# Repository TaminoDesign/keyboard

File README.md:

# keyboard

 <br><br>
 <br><br>
 <br><br>

# Planning
30min (tracked with Lapse)
I have gone for a semi-custom 60% layout, which I think will work well for my needs. It is in a Mac-style layout (e.g., Command key and Option). You can find the sketch of the layout in the repo.

# Schematic
2 hours
Finished with the schematic layout, I had some trouble figuring out how to best arrange them and needed to do some research to find out if the exact placement was important at this point. Turns out the final sizes are only relevant in the next set, so could have saved myself some time. Well, anyway, looking good, moving on to the actual PCB

# PCB
(4:40min tracked with Lapse)
The PCB is finally done. I can't believe it took this long. I had so many issues; the first was realising that the switch cutouts need to be placed in the correct order, as in the schematic. Of course, I only realised this after placing all of them. The next thing to go wrong was realising that I had added too many rows to the schematic, so that had to change. And finally, it turns out I assigned the rows and columns in the wrong order, so I couldn't draw the traces on the board, meaning back to the schematic. To be honest, there still is the issue of switches over my Raspberry Pi; I'm not sure if it will work, but I think/hope that if it doesn't, I can just ignore those and cover them up (they are extra switches), so let's see. But the good news is that it's finished.

# PCB part 2
(2 hours tracked with lapse)
When you think something is finished but it isn't. In my original design, I had switches over top of the Pi; to be honest, I'm not sure if it would have been a problem, but I don't want to risk it. So I had to go and make changes to the schematic, and because I had already added all the tracks to the PCB and then moved switches about, that had to be redone. I mean, I'm glad I decided to do it; getting the PCB and finding that it doesn't work because of strange switch placement would have been so bad.

# Key switch research
(4 hours)
Yep, this was a rabbit hole if there ever was one. I knew a very little bit about the actual switches, just that there are three overall categories. So I really did spend 4 hours researching and comparing. Now I think I always knew I wanted linear switches; I have been typing on laptops my whole life, so I'm just so used to it. What really threw me was the sound: clicky, deep, silent, tappy, loud, medium or quiet. I pretty quickly found out I don't like the clicky to annoying and loud, then found some medium ones that were nice and deep and thought I had found the best ones. But when I thought about them being louder than my laptop, it just seemed too much (I need quiet to concentrate). So, abandoning everything, I started looking into silent switches, found out that silent doesn't really mean silent, just quieter and that even that varied a lot. After many sound tests and reading, I found the TTC Frozen V2 and the Outemu Peach V2. Those seem like the best ones for me; the TTCs are a little more expensive, but they are a lot nicer. I'm really not sure what the budget is, so if constrained, I will go for the Outemu; if not, then the TTC. Both are extremely quiet but still have a deeper sound signature and are not clacky. Well, that concluded my search, just have to find the rest of the components. 

# Case
(4 hours tracked with lapse)
I actually do have experience with CAD, well at least some. I have used Blender and Tinkercad before for small projects. Anyway, Onshape was quite a learning curve; the way you can't just move objects but need to use the transform tool definitely needed some wrapping my heard round. But my worst error was connecting the bottom and the top part of the case. I had no idea Onshape had a 'part' system that connected all objects together if I didn't create a new part. Well, anyway, that took its time; I got the hang of it after some time, and the case is finished. I just hope I have all the measurements and cutouts correct.

Like to the Onshape file: https://cad.onshape.com/documents/2586bd28e0163321bcefb98d/w/22cbb18d3467a40001aad52c/e/a9439bb21eb842022fdd70c8?renderMode=0&uiState=6adaeeaf906bb97b8fde1ceb

# PCB LED
(4 hours tracked with lapse)
Well, I always think I'm done with my PCB, but it always comes back. I mean, I would like to squarely put the blame on a family member who pointed out that LED light would make it much better. So that was a tedious task adding an LED per key and wiring it up. I did some research, and it seems some people put a capacitor in front of every single LED while others don't. I didn't do it as my wiring is complicated enough. But I'm really unsure of what to do. 

# PCB LED part 2
(2:30 hours tracked with lapse)
Well, guess what wouldn't stop haunting me. From some quick research and talking to others in Slack, it seems like I added a bulk capacitor instead of Ceramic Capacitors on the LEDs themselves. So I had to update the schematic, and when I went to update the PCB from the schematic turns out some of the switches are in the wrong place, so those had to be replaced again. Of course, when I saw that some switches were gone, so were some of the Diodes. So that was a process of cleaning up the board and adding the new capacitors to the correct places. But I think this is it; I'm ready to submit.

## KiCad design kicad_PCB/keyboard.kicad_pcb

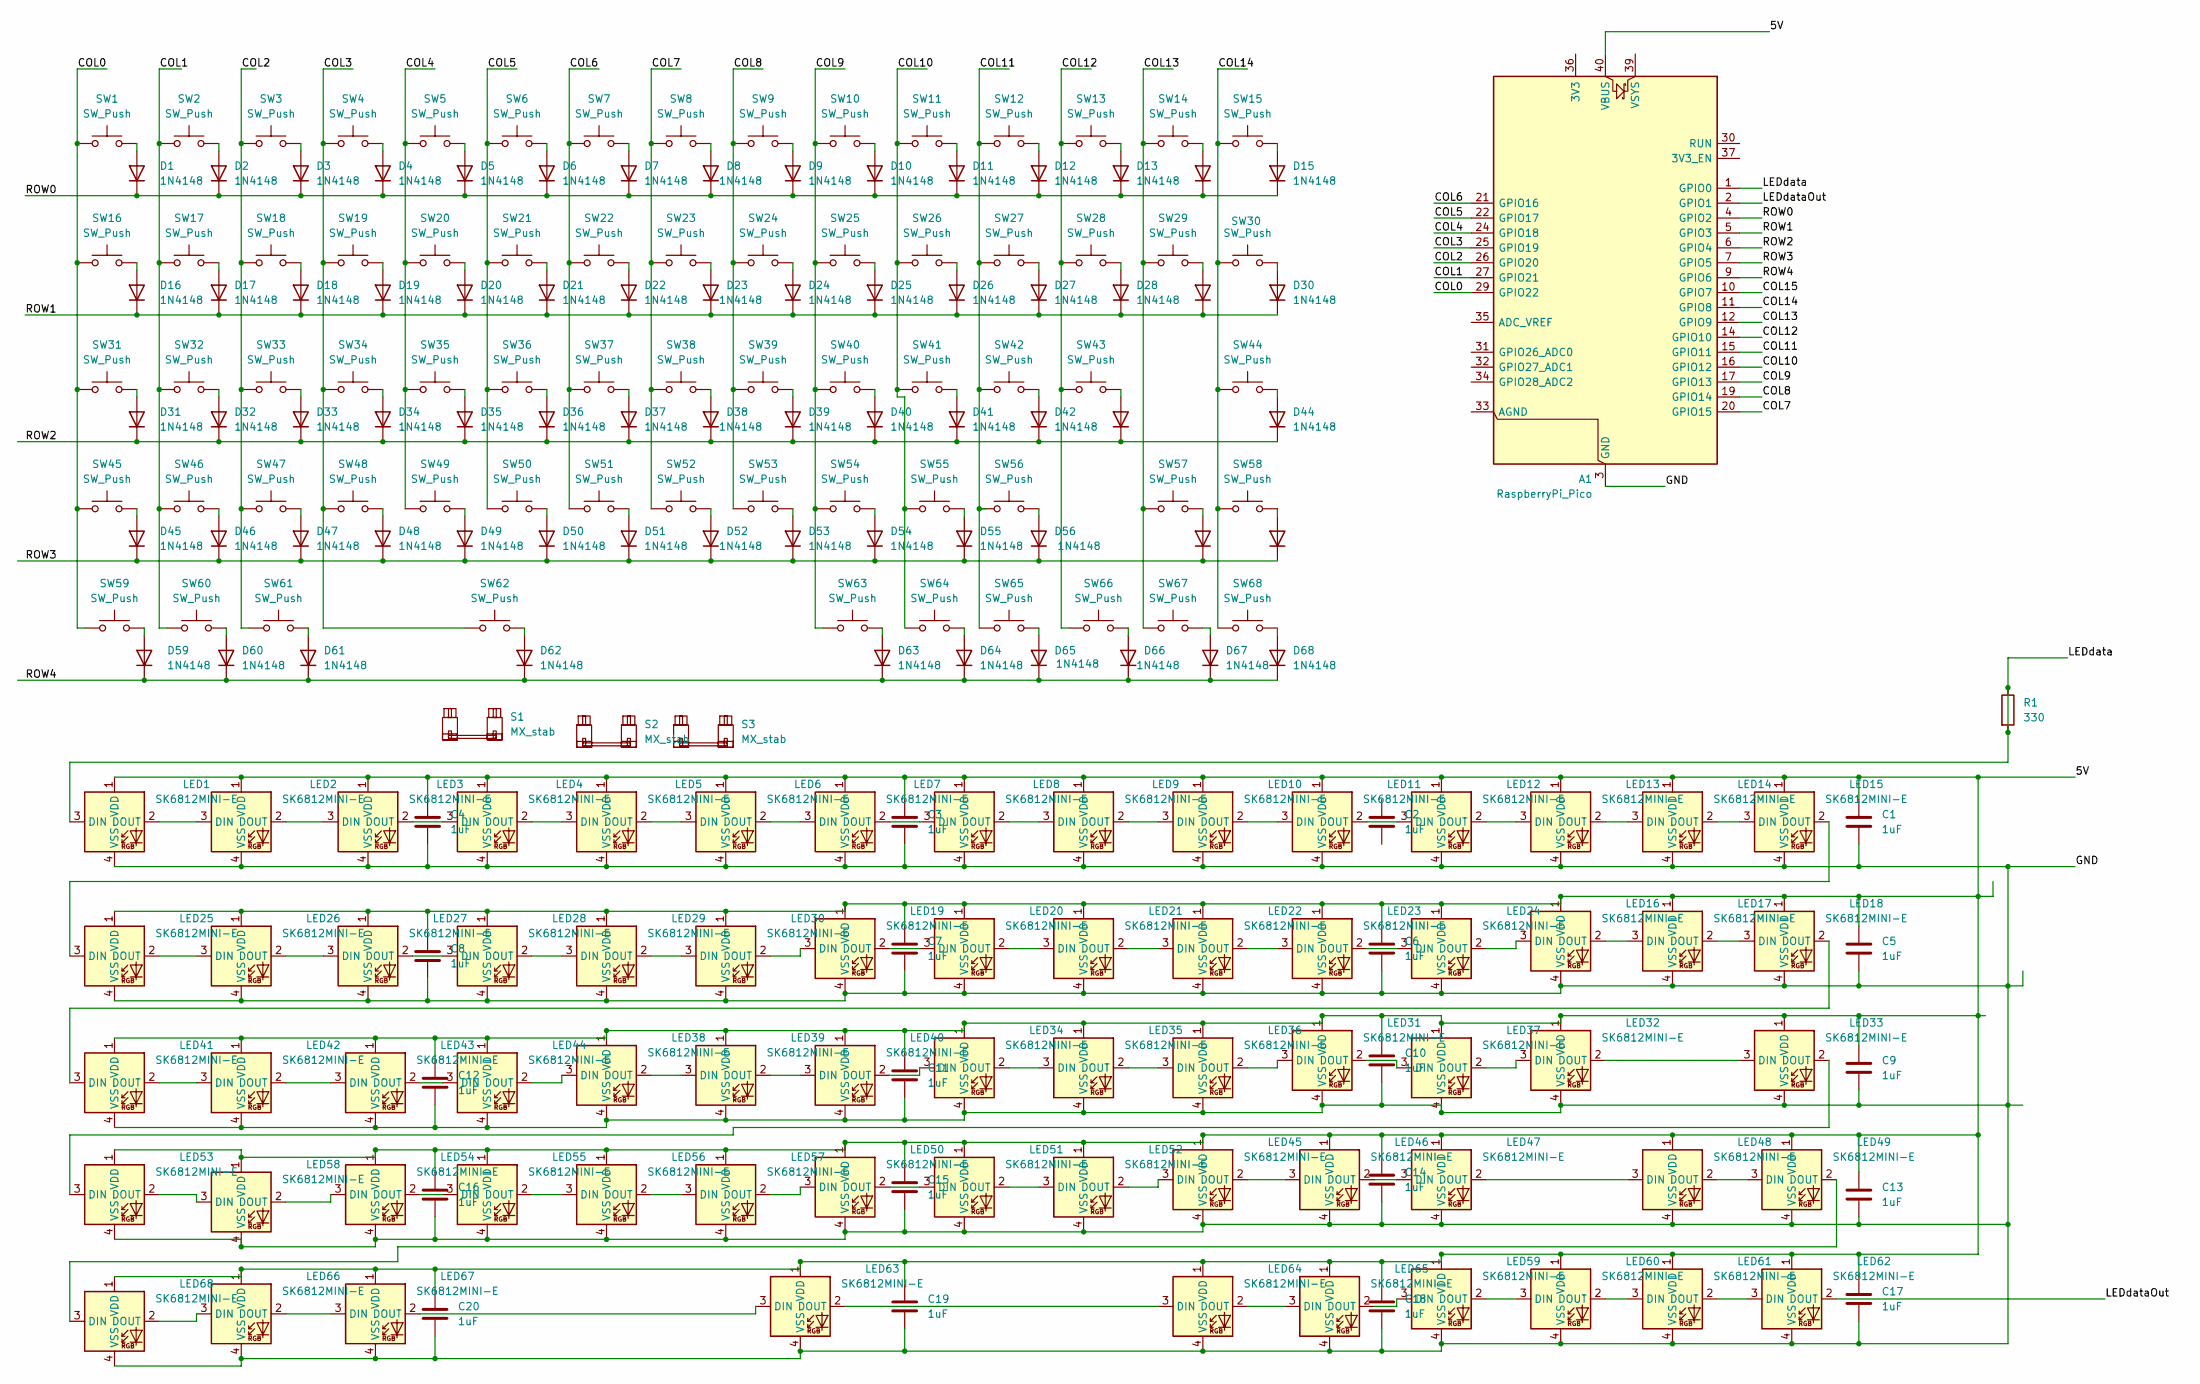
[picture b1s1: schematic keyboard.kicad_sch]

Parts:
A1: RaspberryPi_Pico; RaspberryPi_Pico_Common_THT
C1, C2, C3, C4, C5, C6, C7, C8, C9, C10, C11, C12, C13, C14, C15, C16, C17, C18, C19, C20: 1uF; C_0603_1608Metric
D1, D2, D3, D4, D5, D6, D7, D8, D9, D10, D11, D12, D13, D14, D15, D16, D17, D18, D19, D20, D21, D22, D23, D24, D25, D26, D27, D28, D29, D30, D31, D32, D33, D34, D35, D36, D37, D38, D39, D40, D41, D42, D43, D44, D45, D46, D47, D48, D49, D50, D51, D52, D53, D54, D55, D56, D57, D58, D59, D60, D61, D62, D63, D64, D65, D66, D67, D68: 1N4148; D_DO-35_SOD27_P7.62mm_Horizontal
LED1, LED2, LED3, LED4, LED5, LED6, LED7, LED8, LED9, LED10, LED11, LED12, LED13, LED14, LED15, LED16, LED17, LED18, LED19, LED20, LED21, LED22, LED23, LED24, LED25, LED26, LED27, LED28, LED29, LED30, LED31, LED32, LED33, LED34, LED35, LED36, LED37, LED38, LED39, LED40, LED41, LED42, LED43, LED44, LED45, LED46, LED47, LED48, LED49, LED50, LED51, LED52, LED53, LED54, LED55, LED56, LED57, LED58, LED59, LED60, LED61, LED62, LED63, LED64, LED65, LED66, LED67, LED68: SK6812MINI-E; LED_6028R
R1: 330; R_Axial_DIN0207_L6.3mm_D2.5mm_P10.16mm_Horizontal
S1, S2, S3: MX_stab; STAB_MX_P_6.25u
SW1, SW2, SW3, SW4, SW5, SW6, SW7, SW8, SW9, SW10, SW11, SW12, SW13, SW14, SW15, SW16, SW17, SW18, SW19, SW20, SW21, SW22, SW23, SW24, SW25, SW26, SW27, SW28, SW29, SW30, SW31, SW32, SW33, SW34, SW35, SW36, SW37, SW38, SW39, SW40, SW41, SW42, SW43, SW44, SW45, SW46, SW47, SW48, SW49, SW50, SW51, SW52, SW53, SW54, SW55, SW56, SW57, SW58, SW59, SW60, SW61, SW62, SW63, SW64, SW65, SW66, SW67, SW68: SW_Push; SW_MX_1u

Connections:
/5V: A1.40 (VBUS), C1.1, C3.1, C4.1, C5.1, C6.1, C7.1, C8.1, C9.1, C10.1, C11.1, C12.1, C13.1, C14.1, C15.1, C16.1, C17.1, C18.1, C19.1, C20.1, LED1.1 (VDD), LED2.1 (VDD), LED3.1 (VDD), LED4.1 (VDD), LED5.1 (VDD), LED6.1 (VDD), LED7.1 (VDD), LED8.1 (VDD), LED9.1 (VDD), LED10.1 (VDD), LED11.1 (VDD), LED12.1 (VDD), LED13.1 (VDD), LED14.1 (VDD), LED15.1 (VDD), LED16.1 (VDD), LED17.1 (VDD), LED18.1 (VDD), LED19.1 (VDD), LED20.1 (VDD), LED21.1 (VDD), LED22.1 (VDD), LED23.1 (VDD), LED24.1 (VDD), LED25.1 (VDD), LED26.1 (VDD), LED27.1 (VDD), LED28.1 (VDD), LED29.1 (VDD), LED30.1 (VDD), LED31.1 (VDD), LED32.1 (VDD), LED33.1 (VDD), LED34.1 (VDD), LED35.1 (VDD), LED36.1 (VDD), LED37.1 (VDD), LED38.1 (VDD), LED39.1 (VDD), LED40.1 (VDD), LED41.1 (VDD), LED42.1 (VDD), LED43.1 (VDD), LED44.1 (VDD), LED45.1 (VDD), LED46.1 (VDD), LED47.1 (VDD), LED48.1 (VDD), LED49.1 (VDD), LED50.1 (VDD), LED51.1 (VDD), LED52.1 (VDD), LED53.1 (VDD), LED54.1 (VDD), LED55.1 (VDD), LED56.1 (VDD), LED57.1 (VDD), LED58.1 (VDD), LED59.1 (VDD), LED60.1 (VDD), LED61.1 (VDD), LED62.1 (VDD), LED63.1 (VDD), LED64.1 (VDD), LED65.1 (VDD), LED66.1 (VDD), LED67.1 (VDD), LED68.1 (VDD)
/COL0: A1.29 (GPIO22), SW1.1, SW16.1, SW31.1, SW45.1, SW59.1
/COL1: A1.27 (GPIO21), SW2.1, SW17.1, SW32.1, SW46.1, SW60.1
/COL2: A1.26 (GPIO20), SW3.1, SW18.1, SW33.1, SW47.1, SW61.1
/COL3: A1.25 (GPIO19), SW4.1, SW19.1, SW34.1, SW48.1, SW62.1
/COL4: A1.24 (GPIO18), SW5.1, SW20.1, SW35.1, SW49.1
/COL5: A1.22 (GPIO17), SW6.1, SW21.1, SW36.1, SW50.1
/COL6: A1.21 (GPIO16), SW7.1, SW22.1, SW37.1, SW51.1
/COL7: A1.20 (GPIO15), SW8.1, SW23.1, SW38.1, SW52.1
/COL8: A1.19 (GPIO14), SW9.1, SW24.1, SW39.1, SW53.1
/COL9: A1.17 (GPIO13), SW10.1, SW25.1, SW40.1, SW54.1, SW63.1
/COL10: A1.16 (GPIO12), SW11.1, SW26.1, SW41.1, SW55.1, SW64.1
/COL11: A1.15 (GPIO11), SW12.1, SW27.1, SW42.1, SW56.1, SW65.1
/COL12: A1.14 (GPIO10), SW13.1, SW28.1, SW43.1, SW66.1
/COL13: A1.12 (GPIO9), SW14.1, SW29.1, SW57.1, SW67.1
/COL14: A1.11 (GPIO8), SW15.1, SW30.1, SW44.1, SW58.1, SW68.1
/COL15: A1.10 (GPIO7)
/GND: A1.3 (GND), A1.8 (GND), A1.13 (GND), A1.18 (GND), A1.23 (GND), A1.28 (GND), A1.38 (GND), C1.2, C3.2, C4.2, C5.2, C6.2, C7.2, C8.2, C9.2, C10.2, C11.2, C12.2, C13.2, C14.2, C15.2, C16.2, C17.2, C18.2, C19.2, C20.2, LED1.4 (VSS), LED2.4 (VSS), LED3.4 (VSS), LED4.4 (VSS), LED5.4 (VSS), LED6.4 (VSS), LED7.4 (VSS), LED8.4 (VSS), LED9.4 (VSS), LED10.4 (VSS), LED11.4 (VSS), LED12.4 (VSS), LED13.4 (VSS), LED14.4 (VSS), LED15.4 (VSS), LED16.4 (VSS), LED17.4 (VSS), LED18.4 (VSS), LED19.4 (VSS), LED20.4 (VSS), LED21.4 (VSS), LED22.4 (VSS), LED23.4 (VSS), LED24.4 (VSS), LED25.4 (VSS), LED26.4 (VSS), LED27.4 (VSS), LED28.4 (VSS), LED29.4 (VSS), LED30.4 (VSS), LED31.4 (VSS), LED32.4 (VSS), LED33.4 (VSS), LED34.4 (VSS), LED35.4 (VSS), LED36.4 (VSS), LED37.4 (VSS), LED38.4 (VSS), LED39.4 (VSS), LED40.4 (VSS), LED41.4 (VSS), LED42.4 (VSS), LED43.4 (VSS), LED44.4 (VSS), LED45.4 (VSS), LED46.4 (VSS), LED47.4 (VSS), LED48.4 (VSS), LED49.4 (VSS), LED50.4 (VSS), LED51.4 (VSS), LED52.4 (VSS), LED53.4 (VSS), LED54.4 (VSS), LED55.4 (VSS), LED56.4 (VSS), LED57.4 (VSS), LED58.4 (VSS), LED59.4 (VSS), LED60.4 (VSS), LED61.4 (VSS), LED62.4 (VSS), LED63.4 (VSS), LED64.4 (VSS), LED65.4 (VSS), LED66.4 (VSS), LED67.4 (VSS), LED68.4 (VSS)
/LEDdata: A1.1 (GPIO0), LED1.3 (DIN), R1.1, R1.2
/LEDdataOut: A1.2 (GPIO1), LED62.2 (DOUT)
/ROW0: A1.4 (GPIO2), D1.1 (K), D2.1 (K), D3.1 (K), D4.1 (K), D5.1 (K), D6.1 (K), D7.1 (K), D8.1 (K), D9.1 (K), D10.1 (K), D11.1 (K), D12.1 (K), D13.1 (K), D14.1 (K), D15.1 (K)
/ROW1: A1.5 (GPIO3), D16.1 (K), D17.1 (K), D18.1 (K), D19.1 (K), D20.1 (K), D21.1 (K), D22.1 (K), D23.1 (K), D24.1 (K), D25.1 (K), D26.1 (K), D27.1 (K), D28.1 (K), D29.1 (K), D30.1 (K)
/ROW2: A1.6 (GPIO4), D31.1 (K), D32.1 (K), D33.1 (K), D34.1 (K), D35.1 (K), D36.1 (K), D37.1 (K), D38.1 (K), D39.1 (K), D40.1 (K), D41.1 (K), D42.1 (K), D43.1 (K), D44.1 (K)
/ROW3: A1.7 (GPIO5), D45.1 (K), D46.1 (K), D47.1 (K), D48.1 (K), D49.1 (K), D50.1 (K), D51.1 (K), D52.1 (K), D53.1 (K), D54.1 (K), D55.1 (K), D56.1 (K), D57.1 (K), D58.1 (K)
/ROW4: A1.9 (GPIO6), D59.1 (K), D60.1 (K), D61.1 (K), D62.1 (K), D63.1 (K), D64.1 (K), D65.1 (K), D66.1 (K), D67.1 (K), D68.1 (K)
unnamed: D1.2 (A), SW1.2
unnamed: D2.2 (A), SW2.2
unnamed: D3.2 (A), SW3.2
unnamed: D4.2 (A), SW4.2
unnamed: D5.2 (A), SW5.2
unnamed: D6.2 (A), SW6.2
unnamed: D7.2 (A), SW7.2
unnamed: D8.2 (A), SW8.2
unnamed: D9.2 (A), SW9.2
unnamed: D10.2 (A), SW10.2
unnamed: D11.2 (A), SW11.2
unnamed: D12.2 (A), SW12.2
unnamed: D13.2 (A), SW13.2
unnamed: D14.2 (A), SW14.2
unnamed: D15.2 (A), SW15.2
unnamed: D16.2 (A), SW16.2
unnamed: D17.2 (A), SW17.2
unnamed: D18.2 (A), SW18.2
unnamed: D19.2 (A), SW19.2
unnamed: D20.2 (A), SW20.2
unnamed: D21.2 (A), SW21.2
unnamed: D22.2 (A), SW22.2
unnamed: D23.2 (A), SW23.2
unnamed: D24.2 (A), SW24.2
unnamed: D25.2 (A), SW25.2
unnamed: D26.2 (A), SW26.2
unnamed: D27.2 (A), SW27.2
unnamed: D28.2 (A), SW28.2
unnamed: D29.2 (A), SW29.2
unnamed: D30.2 (A), SW30.2
unnamed: D31.2 (A), SW31.2
unnamed: D32.2 (A), SW32.2
unnamed: D33.2 (A), SW33.2
unnamed: D34.2 (A), SW34.2
unnamed: D35.2 (A), SW35.2
unnamed: D36.2 (A), SW36.2
unnamed: D37.2 (A), SW37.2
unnamed: D38.2 (A), SW38.2
unnamed: D39.2 (A), SW39.2
unnamed: D40.2 (A), SW40.2
unnamed: D41.2 (A), SW41.2
unnamed: D42.2 (A), SW42.2
unnamed: D43.2 (A), SW43.2
unnamed: D44.2 (A), SW44.2
unnamed: D45.2 (A), SW45.2
unnamed: D46.2 (A), SW46.2
unnamed: D47.2 (A), SW47.2
unnamed: D48.2 (A), SW48.2
unnamed: D49.2 (A), SW49.2
unnamed: D50.2 (A), SW50.2
unnamed: D51.2 (A), SW51.2
unnamed: D52.2 (A), SW52.2
unnamed: D53.2 (A), SW53.2
unnamed: D54.2 (A), SW54.2
unnamed: D55.2 (A), SW55.2
unnamed: D56.2 (A), SW56.2
unnamed: D57.2 (A), SW57.2
unnamed: D58.2 (A), SW58.2
unnamed: D59.2 (A), SW59.2
unnamed: D60.2 (A), SW60.2
unnamed: D61.2 (A), SW61.2
unnamed: D62.2 (A), SW62.2
unnamed: D63.2 (A), SW63.2
unnamed: D64.2 (A), SW64.2
unnamed: D65.2 (A), SW65.2
unnamed: D66.2 (A), SW66.2
unnamed: D67.2 (A), SW67.2
unnamed: D68.2 (A), SW68.2
unnamed: LED1.2 (DOUT), LED2.3 (DIN)
unnamed: LED2.2 (DOUT), LED3.3 (DIN)
unnamed: LED3.2 (DOUT), LED4.3 (DIN)
unnamed: LED4.2 (DOUT), LED5.3 (DIN)
unnamed: LED5.2 (DOUT), LED6.3 (DIN)
unnamed: LED6.2 (DOUT), LED7.3 (DIN)
unnamed: LED7.2 (DOUT), LED8.3 (DIN)
unnamed: LED8.2 (DOUT), LED9.3 (DIN)
unnamed: LED9.2 (DOUT), LED10.3 (DIN)
unnamed: LED10.2 (DOUT), LED11.3 (DIN)
unnamed: LED11.2 (DOUT), LED12.3 (DIN)
unnamed: LED12.2 (DOUT), LED13.3 (DIN)
unnamed: LED13.2 (DOUT), LED14.3 (DIN)
unnamed: LED14.2 (DOUT), LED15.3 (DIN)
unnamed: LED15.2 (DOUT), LED25.3 (DIN)
unnamed: LED16.3 (DIN), LED24.2 (DOUT)
unnamed: LED16.2 (DOUT), LED17.3 (DIN)
unnamed: LED17.2 (DOUT), LED18.3 (DIN)
unnamed: LED18.2 (DOUT), LED41.3 (DIN)
unnamed: LED19.3 (DIN), LED30.2 (DOUT)
unnamed: LED19.2 (DOUT), LED20.3 (DIN)
unnamed: LED20.2 (DOUT), LED21.3 (DIN)
unnamed: LED21.2 (DOUT), LED22.3 (DIN)
unnamed: LED22.2 (DOUT), LED23.3 (DIN)
unnamed: LED23.2 (DOUT), LED24.3 (DIN)
unnamed: LED25.2 (DOUT), LED26.3 (DIN)
unnamed: LED26.2 (DOUT), LED27.3 (DIN)
unnamed: LED27.2 (DOUT), LED28.3 (DIN)
unnamed: LED28.2 (DOUT), LED29.3 (DIN)
unnamed: LED29.2 (DOUT), LED30.3 (DIN)
unnamed: LED31.3 (DIN), LED36.2 (DOUT)
unnamed: LED31.2 (DOUT), LED37.3 (DIN)
unnamed: LED32.3 (DIN), LED37.2 (DOUT)
unnamed: LED32.2 (DOUT), LED33.3 (DIN)
unnamed: LED33.2 (DOUT), LED53.3 (DIN)
unnamed: LED34.3 (DIN), LED40.2 (DOUT)
unnamed: LED34.2 (DOUT), LED35.3 (DIN)
unnamed: LED35.2 (DOUT), LED36.3 (DIN)
unnamed: LED38.3 (DIN), LED44.2 (DOUT)
unnamed: LED38.2 (DOUT), LED39.3 (DIN)
unnamed: LED39.2 (DOUT), LED40.3 (DIN)
unnamed: LED41.2 (DOUT), LED42.3 (DIN)
unnamed: LED42.2 (DOUT), LED43.3 (DIN)
unnamed: LED43.2 (DOUT), LED44.3 (DIN)
unnamed: LED45.3 (DIN), LED52.2 (DOUT)
unnamed: LED45.2 (DOUT), LED46.3 (DIN)
unnamed: LED46.2 (DOUT), LED47.3 (DIN)
unnamed: LED47.2 (DOUT), LED48.3 (DIN)
unnamed: LED48.2 (DOUT), LED49.3 (DIN)
unnamed: LED49.2 (DOUT), LED68.3 (DIN)
unnamed: LED50.3 (DIN), LED57.2 (DOUT)
unnamed: LED50.2 (DOUT), LED51.3 (DIN)
unnamed: LED51.2 (DOUT), LED52.3 (DIN)
unnamed: LED53.2 (DOUT), LED58.3 (DIN)
unnamed: LED54.3 (DIN), LED58.2 (DOUT)
unnamed: LED54.2 (DOUT), LED55.3 (DIN)
unnamed: LED55.2 (DOUT), LED56.3 (DIN)
unnamed: LED56.2 (DOUT), LED57.3 (DIN)
unnamed: LED59.3 (DIN), LED65.2 (DOUT)
unnamed: LED59.2 (DOUT), LED60.3 (DIN)
unnamed: LED60.2 (DOUT), LED61.3 (DIN)
unnamed: LED61.2 (DOUT), LED62.3 (DIN)
unnamed: LED63.3 (DIN), LED67.2 (DOUT)
unnamed: LED63.2 (DOUT), LED64.3 (DIN)
unnamed: LED64.2 (DOUT), LED65.3 (DIN)
unnamed: LED66.3 (DIN), LED68.2 (DOUT)
unnamed: LED66.2 (DOUT), LED67.3 (DIN)

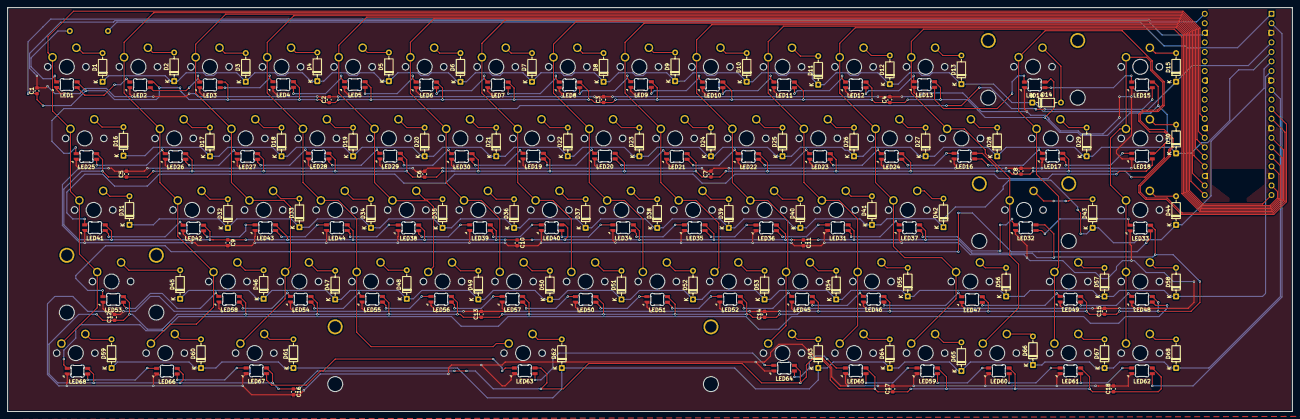
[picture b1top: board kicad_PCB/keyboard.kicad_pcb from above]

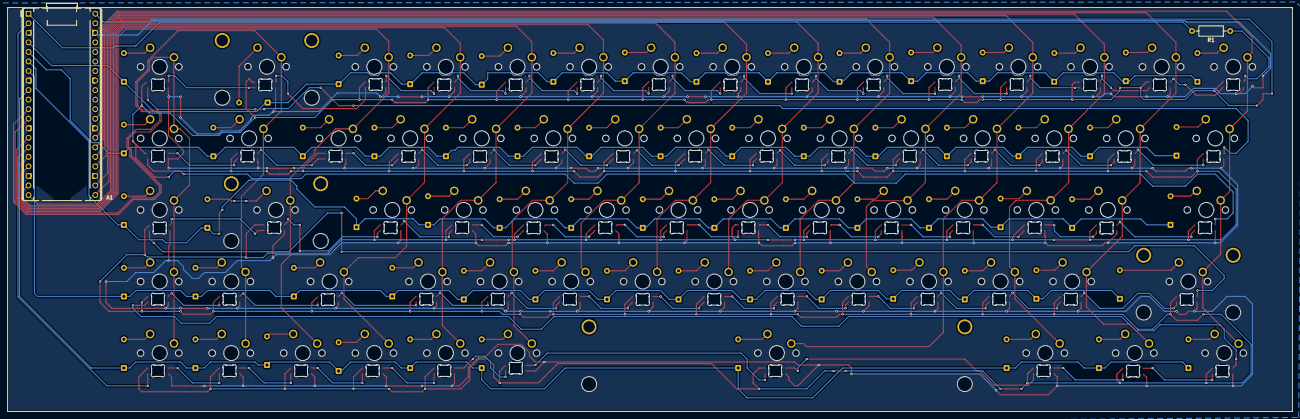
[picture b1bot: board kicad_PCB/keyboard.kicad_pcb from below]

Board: 2 copper layers, 342.0 x 107.5 mm, 228 parts (2 on the bottom side), 159 nets.

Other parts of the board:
S1#2: MX_stab; STAB_MX_P_2u

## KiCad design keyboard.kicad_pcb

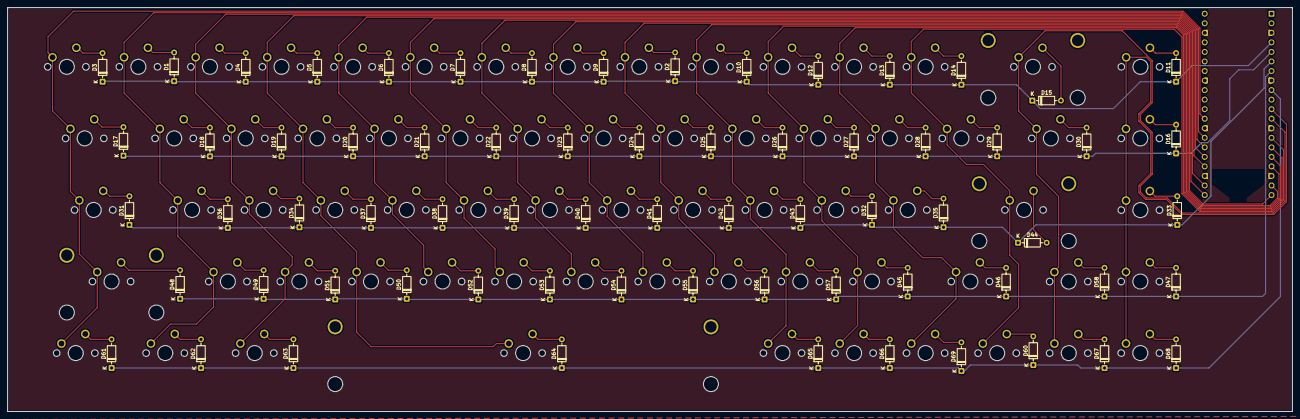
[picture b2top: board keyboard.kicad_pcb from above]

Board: 2 copper layers, 342.0 x 107.5 mm, 141 parts (1 on the bottom side), 89 nets.

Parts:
A1: RaspberryPi_Pico; RaspberryPi_Pico_Common_THT
D1, D2, D3, D4, D5, D6, D7, D8, D9, D10, D11, D12, D13, D14, D15, D16, D17, D18, D19, D20, D21, D22, D23, D24, D25, D26, D27, D28, D29, D30, D31, D32, D33, D34, D35, D36, D37, D38, D39, D40, D41, D42, D43, D44, D45, D46, D47, D48, D49, D50, D51, D52, D53, D54, D55, D56, D57, D58, D60, D61, D62, D63, D64, D65, D66, D67, D68, D69: 1N4148; D_DO-35_SOD27_P7.62mm_Horizontal
S1: MX_stab; STAB_MX_P_2u
S2, S3: MX_stab; STAB_MX_P_2.25u
S4: MX_stab; STAB_MX_P_6.25u
SW1, SW2, SW3, SW4, SW5, SW6, SW7, SW8, SW9, SW10, SW11, SW12, SW13, SW14, SW15, SW16, SW17, SW18, SW19, SW20, SW21, SW22, SW23, SW24, SW25, SW26, SW27, SW28, SW29, SW30, SW31, SW32, SW33, SW34, SW35, SW36, SW37, SW38, SW39, SW40, SW41, SW42, SW43, SW44, SW45, SW46, SW47, SW48, SW49, SW50, SW51, SW52, SW53, SW54, SW55, SW56, SW57, SW58, SW60, SW61, SW62, SW63, SW64, SW65, SW66, SW67, SW68, SW69: SW_Push; SW_MX_1u

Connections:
/COL0: A1.29 (GPIO22), SW1.1, SW16.1, SW31.1, SW45.1, SW60.1
/COL1: A1.27 (GPIO21), SW2.1, SW17.1, SW32.1, SW46.1, SW61.1
/COL2: A1.26 (GPIO20), SW3.1, SW18.1, SW33.1, SW47.1, SW62.1
/COL3: A1.25 (GPIO19), SW4.1, SW19.1, SW34.1, SW48.1, SW63.1
/COL4: A1.24 (GPIO18), SW5.1, SW20.1, SW35.1, SW49.1
/COL5: A1.22 (GPIO17), SW6.1, SW21.1, SW36.1, SW50.1
/COL6: A1.21 (GPIO16), SW7.1, SW22.1, SW37.1, SW51.1
/COL7: A1.20 (GPIO15), SW8.1, SW23.1, SW38.1, SW52.1
/COL8: A1.19 (GPIO14), SW9.1, SW24.1, SW39.1, SW53.1
/COL9: A1.17 (GPIO13), SW10.1, SW25.1, SW40.1, SW54.1, SW64.1
/COL10: A1.16 (GPIO12), SW11.1, SW26.1, SW41.1, SW55.1, SW65.1
/COL11: A1.15 (GPIO11), SW12.1, SW27.1, SW42.1, SW56.1, SW66.1
/COL12: A1.14 (GPIO10), SW13.1, SW28.1, SW43.1, SW67.1
/COL13: A1.12 (GPIO9), SW14.1, SW29.1, SW57.1, SW68.1
/COL14: A1.11 (GPIO8), SW15.1, SW30.1, SW44.1, SW58.1, SW69.1
/ROW0: A1.4 (GPIO2), D1.1 (K), D2.1 (K), D3.1 (K), D4.1 (K), D5.1 (K), D6.1 (K), D7.1 (K), D8.1 (K), D9.1 (K), D10.1 (K), D11.1 (K), D12.1 (K), D13.1 (K), D14.1 (K), D15.1 (K)
/ROW1: A1.5 (GPIO3), D16.1 (K), D17.1 (K), D18.1 (K), D19.1 (K), D20.1 (K), D21.1 (K), D22.1 (K), D23.1 (K), D24.1 (K), D25.1 (K), D26.1 (K), D27.1 (K), D28.1 (K), D29.1 (K), D30.1 (K)
/ROW2: A1.6 (GPIO4), D31.1 (K), D32.1 (K), D33.1 (K), D34.1 (K), D35.1 (K), D36.1 (K), D37.1 (K), D38.1 (K), D39.1 (K), D40.1 (K), D41.1 (K), D42.1 (K), D43.1 (K), D44.1 (K)
/ROW3: A1.7 (GPIO5), D45.1 (K), D46.1 (K), D47.1 (K), D48.1 (K), D49.1 (K), D50.1 (K), D51.1 (K), D52.1 (K), D53.1 (K), D54.1 (K), D55.1 (K), D56.1 (K), D57.1 (K), D58.1 (K)
/ROW4: A1.9 (GPIO6), D60.1 (K), D61.1 (K), D62.1 (K), D63.1 (K), D64.1 (K), D65.1 (K), D66.1 (K), D67.1 (K), D68.1 (K), D69.1 (K)
unnamed: A1.3 (GND), A1.8 (GND), A1.13 (GND), A1.18 (GND), A1.23 (GND), A1.28 (GND), A1.38 (GND)
unnamed: D3.2 (A), SW1.2
unnamed: D62.2 (A), SW61.2
unnamed: D19.2 (A), SW18.2
unnamed: D20.2 (A), SW19.2
unnamed: D38.2 (A), SW35.2
unnamed: D7.2 (A), SW6.2
unnamed: D8.2 (A), SW7.2
unnamed: D41.2 (A), SW38.2
unnamed: D25.2 (A), SW24.2
unnamed: D10.2 (A), SW10.2
unnamed: D27.2 (A), SW26.2
unnamed: D28.2 (A), SW27.2
unnamed: D44.2 (A), SW43.2
unnamed: D15.2 (A), SW14.2
unnamed: D68.2 (A), SW69.2
unnamed: D48.2 (A), SW45.2
unnamed: D18.2 (A), SW17.2
unnamed: D4.2 (A), SW3.2
unnamed: D5.2 (A), SW4.2
unnamed: D21.2 (A), SW20.2
unnamed: D39.2 (A), SW36.2
unnamed: D40.2 (A), SW37.2
unnamed: D55.2 (A), SW52.2
unnamed: D56.2 (A), SW53.2
unnamed: D43.2 (A), SW40.2
unnamed: D12.2 (A), SW11.2
unnamed: D13.2 (A), SW12.2
unnamed: D14.2 (A), SW13.2
unnamed: D30.2 (A), SW29.2
unnamed: D47.2 (A), SW58.2
unnamed: D31.2 (A), SW31.2
unnamed: D49.2 (A), SW46.2
unnamed: D51.2 (A), SW47.2
unnamed: D37.2 (A), SW34.2
unnamed: D6.2 (A), SW5.2
unnamed: D22.2 (A), SW21.2
unnamed: D23.2 (A), SW22.2
unnamed: D24.2 (A), SW23.2
unnamed: D42.2 (A), SW39.2
unnamed: D65.2 (A), SW64.2
unnamed: D66.2 (A), SW65.2
unnamed: D35.2 (A), SW42.2
unnamed: D29.2 (A), SW28.2
unnamed: D16.2 (A), SW30.2
unnamed: D61.2 (A), SW60.2
unnamed: D1.2 (A), SW2.2
unnamed: D34.2 (A), SW33.2
unnamed: D64.2 (A), SW63.2
unnamed: D52.2 (A), SW49.2
unnamed: D53.2 (A), SW50.2
unnamed: D54.2 (A), SW51.2
unnamed: D9.2 (A), SW8.2
unnamed: D2.2 (A), SW9.2
unnamed: D26.2 (A), SW25.2
unnamed: D32.2 (A), SW41.2
unnamed: D46.2 (A), SW56.2
unnamed: D58.2 (A), SW57.2
unnamed: D33.2 (A), SW44.2
unnamed: D17.2 (A), SW16.2
unnamed: D36.2 (A), SW32.2
unnamed: D63.2 (A), SW62.2
unnamed: D50.2 (A), SW48.2
unnamed: D57.2 (A), SW54.2
unnamed: D45.2 (A), SW55.2
unnamed: D69.2 (A), SW66.2
unnamed: D60.2 (A), SW67.2
unnamed: D67.2 (A), SW68.2
unnamed: D11.2 (A), SW15.2
